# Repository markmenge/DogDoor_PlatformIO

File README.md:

This is an AI experiment. It is a work-in-progress. Check back later for when things start working.

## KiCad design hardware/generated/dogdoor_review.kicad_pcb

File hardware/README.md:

# DogDoor carrier PCB: engineering review draft

**Do not order this revision.** This is a reproducible design/routing exercise,
not a fabrication-approved or safety-certified door controller. No order is
placed, and no production Gerber ZIP is supplied until the checks below pass.
The existing firmware is unchanged.

## Open the project

Open `generated/dogdoor_review.kicad_pro` in KiCad 7. The project includes an
editable schematic, a placed board, a circuit manifest, and review BOM/placement
CSVs. The schematic uses embedded pin-by-pin review symbols, so it does not
need a downloaded symbol library. Footprints use your installed KiCad libraries.
The board is intentionally roomy: 140 x 100 mm, two copper layers.

J3 uses the bundled `BarrelJack_Horizontal.step` visual model in KiCad's 3D
viewer, rotated 90 degrees to match the existing PJ-102AH footprint. Both the
placed and routed boards reference it relative to the project directory; no
installed 3D library is needed for J3. This is a generic horizontal barrel-jack
visual approximation, not a manufacturer-certified PJ-102AH mechanical model.
The pads, wiring, and part selection are unchanged.
Model source: [KiCad packages3D, release 10.0.0](https://gitlab.com/kicad/libraries/kicad-packages3D/-/blob/10.0.0/Connector_BarrelJack.3dshapes/BarrelJack_Horizontal.step).
License: [CC BY-SA 4.0 with KiCad library exception](https://www.kicad.org/libraries/license/).

The bundled `Heltec_WiFi_Kit_32_V2.wrl` shows a visual-only module assembly
across J1/J2, including both socket rows, white PCB, OLED with cyan HELTEC text,
USB connector, and buttons. It is attached once to J1; J2's standalone socket
model is omitted because the assembly includes it. The header spacing is
22.86 mm with 18 pins per row at 2.54 mm pitch, USB toward pin 1 / board top.
Socket height is assumed to be 8.5 mm; module body is approximated as
26.06 x 50 x 1.6 mm. This is not a certified clearance or enclosure model.
No electrical features are changed. Run `hardware/heltec_model.py` to rebuild
the model alone; board generation rebuilds it with the selected row spacing.

## Confirmed requirements and assumptions

- Heltec WiFi Kit 32 V2, two 18-pin rows, USB end toward the top of the PCB.
- Along-row pitch is 2.54 mm (0.1 inch).
- Row separation is your confirmed **22.86 mm center-to-center (0.9 inch)**.
   Print `generated/socket_fit_check.pdf` at 100% and compare the real module
   as a final check before ordering; header sockets still need adequate height.
- Regulated 5 V, 3 A adapter, 2.1 mm center-positive plug.
- Two yellow TT motors, separate electrical outputs, same direction commands.
  They are NOT connected electrically in parallel on this PCB.
- HC-SR501 PIR outputs are assumed to be 3.3 V, not 5 V. Measure them first.
- Factory assembles fitted SMD parts; you solder sockets, connectors, and bulk
  capacitors. Sensor headers can be omitted and wires soldered into their holes.

## Circuit choices

U1/U2 are TI **DRV8876PWPR** HTSSOP MOSFET bridges. PMODE is HIGH for two-input
PWM control, compatible with the existing GPIO25/GPIO26 direction interface.
Both LOW means **coast**, not braking. Never assume the winch holds the door
when power is off: provide mechanical retention and independent obstruction
protection. Driver outputs must never be connected together.

Each bridge has a nominal **1.0 A current limit**, not a 2 A setting. VREF is
nominally 1.65 V from a 10k/10k divider on the Heltec 3.3 V output. A 1.50k
IPROPI resistor and the datasheet's 1100 uA/A current mirror give:

`Itrip = 1.65 / (1500 * 0.0011) = 1.0 A`

This is winding current regulation, not a precise total adapter-current limit.
Sense tolerance, startup overshoot, capacitor inrush, motor loading, and ESP32
Wi-Fi consumption still require bench measurement. Two TT motors can exceed
the 3 A supply at stall without limiting. The limited motors may not lift the
door. Do not raise the limit blindly; measure load and reassess supply/thermal
requirements. The driver's 3.5 A specification is a peak rating, not permission
to run that current continuously on this layout.

IMODE floats intentionally: fixed-off-time chopping with latched-off overcurrent
protection. Do not add a pull-down there. Removing/reclosing the stop loop resets
sleep and can re-enable the outputs if the firmware still commands movement.

J5 is a normally-closed stop-loop connection to nSLEEP. With it open, both
drivers are disabled. This is a bench inhibit, not a certified emergency stop;
it causes coasting and does not cut power. Use a proper motor-power disconnect
and mechanical safety measures for the installed door.

VM is fed through a 3 A fuse. The driver requires **at least 4.5 V at its VM pin**:
your nominal 5 V leaves only 0.5 V for adapter sag, cable, jack, fuse, and traces.
Measure under simultaneous starting and worst permitted load. F1 requires an
inrush/time-current review; it does not regulate current or protect an animal.
There is **no reverse-polarity or wrong-voltage protection** in this draft.
Do not plug an Arduino 9 V/12 V adapter into the same-looking socket.

The controller branch uses SS34 isolation, a low-DCR ferrite, 470 uF, and ceramic
decoupling. It shares the adapter with VM: filtering does not fix sustained supply
sag. JP1 disconnects the Heltec 5 V feed. Remove JP1 before powering by USB;
do not rely on the carrier diode to resolve the Heltec's internal power paths.
Confirm the revision-specific Heltec schematic before simultaneous power sources.

The bridges have 22 nF charge-pump flying capacitors, 100 nF VCP-to-VM capacitors,
100 nF VM bypasses, and 10 uF local ceramics. Add 100 nF suppression capacitors
directly at each motor, with short leads and twisted motor wires. The bulk
capacitors do not substitute for short, low-resistance motor power wiring.

GPIO35 receives the combined open-drain fault outputs. GPIO34 and GPIO36 receive
the two current-sense signals. Existing firmware does not read these signals:
do not assume an automatic stop on driver fault or excessive load is implemented.

## Connection table

| Reference | Connection |
| --- | --- |
| J1/J2 | Female Heltec sockets; pin 1 at USB end on each row |
| J3 | CUI PJ-102AH, center-positive 5 V only, 2.1 mm |
| J4 | Alternate power screw terminal: pin 1 +5 V, pin 2 GND; use ONE input |
| J6 | Motor A: pins 1/2 motor leads |
| J7 | Motor B: pins 1/2 motor leads; swap one motor's leads if mechanically opposed |
| J8/J9 | PIR inside/outside: pin 1 +5 V, pin 2 OUT (3.3 V only), pin 3 GND |
| J10/J11 | Open/closed reed: pin 1 switch signal, pin 2 GND; passive contacts only |
| J5 | Normally-closed bench inhibit loop; open = both bridges disabled |
| JP1 | Shunt for carrier-powered Heltec; REMOVE before USB power |

Socket row labels and numbers come from the local V2 pinout PDF, not from a
generic ESP32 DevKit footprint. Vext, OLED pins, and unused module pins are left
unconnected. Only one module 3.3 V header pin feeds the reference/control circuit.

GPIO2 and GPIO12 are boot straps. The fitted R40/R42 zero-ohm links preserve the
current firmware, but cold boots must be tested with PIR HIGH/LOW and reed open/
closed. No external pull-up is added to GPIO12. Before production, prefer moving
PIR_OUT to GPIO22 and LIMIT_CLOSE to GPIO27: remove R40/R42, fit R41/R43, and
change the corresponding firmware constants. Never fit both options at once.

## Generate again

From the workspace root in PowerShell:

```powershell
& 'C:/Program Files/Python311/python.exe' hardware/generate.py --self-test
& 'D:/Program Files/KiCad/7.0/bin/python.exe' hardware/generate.py
& 'D:/Program Files/KiCad/7.0/bin/python.exe' hardware/generate.py --row-spacing 22.86
& 'D:/Program Files/KiCad/7.0/bin/python.exe' hardware/generate.py --route "$env:LOCALAPPDATA/DogDoorPCB/freerouting-2.5.0/freerouting-2.5.0.jar"
& 'C:/Program Files/Python311/python.exe' hardware/review.py
& 'C:/Program Files/Python311/python.exe' hardware/review.py --session hardware/generated/dogdoor_review.ses
& 'D:/Program Files/KiCad/7.0/bin/python.exe' hardware/generate.py --import-routing hardware/generated/dogdoor_review.routing.json
```

**Generation overwrites generated files, including manual PCB edits.** Make a
separate working copy of the project before editing. The generator checks circuit
assignments, KiCad-parsed schematic connectivity, and all assigned PCB pads.
It does not certify analog behavior, footprint fit, component sourcing, or safety.

FreeRouting 2.5.0 was downloaded from the official GitHub release and checked
against its published SHA-256. Its native Windows build crashed on board snapshot
serialization, so use the JAR with a portable Java 25 runtime under local app-data.
The generator discovers that runtime automatically; `--java` can override it.
Your existing system Java installation is unchanged.

## Routing and remaining PCB work

The generator exports DSN and FreeRouting produces SES. In PCB Editor, use
**File > Import > Specctra Session** to import `dogdoor_review.ses`, then save.
The autorouter is a layout assistant, not electrical sign-off.

1. **Fit first.** Print a 1:1 board drawing with scaling disabled; verify the
   printed 2.54 mm pitch and row spacing with a ruler, then compare your module.
   Measure pin centers, not outside edges. Both rows must enter female sockets
   without bending pins. Verify USB overhang/access and antenna position.
2. **Power paths.** Highlight INPUT_5V, VM, MOTOR_A1/A2, and MOTOR_B1/B2. Their
   draft net class requests 1.2 mm tracks and larger vias; the tiny HTSSOP pads
   need short 0.3 mm escape sections. Review actual copper width, neck-down
   length, via ampacity, voltage drop, and temperature, not only net-class names.
   Use wider copper pours for the 3 A feeder where practical. Route each motor's
   return through the driver/ground plane, not through the module/sensor area.
3. **Ground and heat.** Add continuous GND pours on both layers and refill with
   B. Connect U1/U2 exposed pads and nearby ground pins to substantial copper,
   with thermal vias and stitching. Do not make the ESP32 ground path the sole
   motor return. Confirm copper area against TI's layout/thermal guidance. The
   standard footprint includes 0.2 mm thermal drills: confirm fabricator support
   and solder-wicking/paste requirements with the assembly house.
4. **Critical capacitors.** Inspect C10/C20 (CPH-CPL), C11/C21 (VCP-VM), and
   C12/C22 (VM-GND). Short direct loops matter; fix router detours around these
   pins. R10/R20 should connect directly to IPROPI and local quiet ground. Keep
   VREF/current-sense signals away from motor switching paths.
5. **Antenna.** Confirm the actual antenna outline. The draft bottom-of-module
   keep-out excludes copper/tracks/vias on both layers. Expand or move it to the
   module maker's required region; avoid nearby metal, motors, and enclosure walls.
6. **Rules and labels.** Run Inspect > Design Rules Checker. Fix every clearance,
   short, unrouted connection, courtyard conflict, and edge violation; review
   warnings individually. Do not blindly exclude errors. Move silk away from pads,
   enlarge illegible labels, and mark polarity/pin 1 clearly. Check the socket's
   female numbering versus the view in the PDF, not only 3D appearance.
7. **Schematic checks.** Run schematic ERC manually (KiCad 7 has no CLI ERC here).
   The embedded review symbols use passive pins and therefore do not catch all
   electrical-type mistakes; independently review the TI PWP pinout and every
   power/control connection. Do not update the PCB from a generic replacement
   symbol without checking pin mapping and footprint association.

## Actual routing result and repairs

**Latest manually repaired board:** `generated/dogdoor_review_routed.kicad_pcb`.
The saved `generated/DRC.rpt` dated 2026-10-12 reports zero DRC violations,
zero unconnected pads, and zero footprint errors. The following routing counts
describe the initial autorouter output, before those manual repairs. Clean DRC
does not approve motor-current capacity, thermal layout, sourcing, or safety.
Do not regenerate or reimport the old routing session over the repaired board.

Open `generated/dogdoor_review_routed.kicad_pro` for the routed draft. The placed
project is separate. Regeneration overwrites both, so make a copy before manual
layout work. `review.py` requires PyMuPDF and sexpdata in system Python, while
`generate.py` uses KiCad's bundled Python.

The Java FreeRouting run completed three passes and reported 12 unrouted items
with no router-rule violations. The imported KiCad board contains 43 vias.
KiCad's independent `generated/routed_drc.txt` identifies **8 missing connections,
50 minimum-track-width errors, and 12 dangling-track/via warnings**. No clearance,
short-circuit, or footprint errors were reported. This is not a clean DRC result.

In PCB Editor, run Inspect > Design Rules Checker, click each item to locate it,
and use Highlight Net to follow the intended connection. Route with X from the
existing pad/track endpoint, not from an approximate point on the drawing.

| Unfinished net | Starting point / repair target |
| --- | --- |
| CLOSE | R5 pad 1 to the existing CLOSE route |
| FAULT | U2 pad 4 to the existing shared FAULT route |
| GND | Join the driver-area ground islands with properly reviewed ground copper |
| MOTOR_A2 | U1 OUT2/pad 10 escape to J6 pad 2 |
| MOTOR_B2 | U2 OUT2/pad 10 escape to J7 pad 2 |
| VM (three gaps) | Connect both VM/pad 11 escapes, local C11/C21 VM pads, and the shared motor supply |

FreeRouting necked down some routes to **0.15 mm**, narrower than the board's
**0.25 mm minimum**. Reroute/widen those sections; do not just lower the rule or
exclude the errors. Motor/power copper needs the wider 1.2 mm nominal route
outside short pad escapes, with further voltage-drop/thermal review as above.
Some preplaced escape stubs are locked: unlock only the affected track before
editing, preserving the IC pin-to-net connection. Remove genuinely unused stub
ends and one-layer-only vias after completing their nets, then rerun DRC.

## Factory assembly and ordering gate

The review BOM deliberately says REVIEW_REQUIRED for unselected supplier parts.
It is **not an upload-ready JLCPCB BOM**. Choose an assembly house, reserve actual
stock, and verify exact manufacturer part numbers, packages, voltage ratings,
capacitor DC-bias derating, ferrite DCR/current rating, jack current rating, and
connector hole sizes. Confirm DRV8876PWPR, not a different QFN package.

The placement CSV uses a bottom-left board origin with positive Y upward, top
side only. Factory rotation conventions vary: verify every pin-1/polarity preview,
especially the ICs and diode. Through-hole connectors and electrolytics are
marked HAND, and R41/R43 are DNP. Match the approved board version to BOM/CPL.

Only after independent electrical/layout review, fit checks, BOM review, and
zero unresolved manufacturing DRC errors should you plot Gerbers and Excellon
drills from the approved board. Inspect them in GerbView and the manufacturer's
preview. Request a small prototype batch, not a production run. This exercise
does not include paying for or submitting an order.

## First prototype bring-up

1. Keep the door mechanism disconnected. Remove the module, both motors, JP1,
   and the J5 inhibit loop. Inspect solder/polarity and check for power shorts.
2. Use a current-limited bench supply for first power-on; verify VM and filtered
   5 V before inserting the module. The ordinary 3 A adapter is not a substitute
   for a bench current limit during initial fault finding.
3. Power off, insert the module in the confirmed orientation, and enable its
   selected power path. Check 3.3 V, VREF (~1.65 V), nSLEEP LOW with J5 open,
   and output coasting. Leave the motor terminals unconnected for logic testing.
4. Connect one unloaded motor, enable J5, and pulse a direction briefly. Verify
   polarity, stop-loop behavior, sense current, and supply minimum voltage.
   Repeat for the other motor before running both. Do not deliberately hold a
   motor stalled to test the limit; use controlled load equipment.
5. Add suppression capacitors at the motors, verify both drive the drum in the
   same mechanical direction, then measure simultaneous-start and loaded current.
   Monitor IC/fuse/connector temperature and ESP32 reset behavior. Stop if the
   VM supply drops below specification or the assembly heats excessively.
6. Verify all cold-boot sensor states, both limits, wire-break cases, inhibit,
   OTA, Wi-Fi loss, and power-off behavior. Current firmware has no debug run
   timeout and ignores the new current/fault inputs; fix the safety behavior
   before connecting a working door. PIRs are not obstruction safety sensors.

## References

- Local `../WIFI_Kit_32_pinoutDiagram_V2.pdf` and V2 schematic.
- TI DRV8876 datasheet: https://www.ti.com/lit/ds/symlink/drv8876.pdf
- FreeRouting releases: https://github.com/freerouting/freerouting/releases

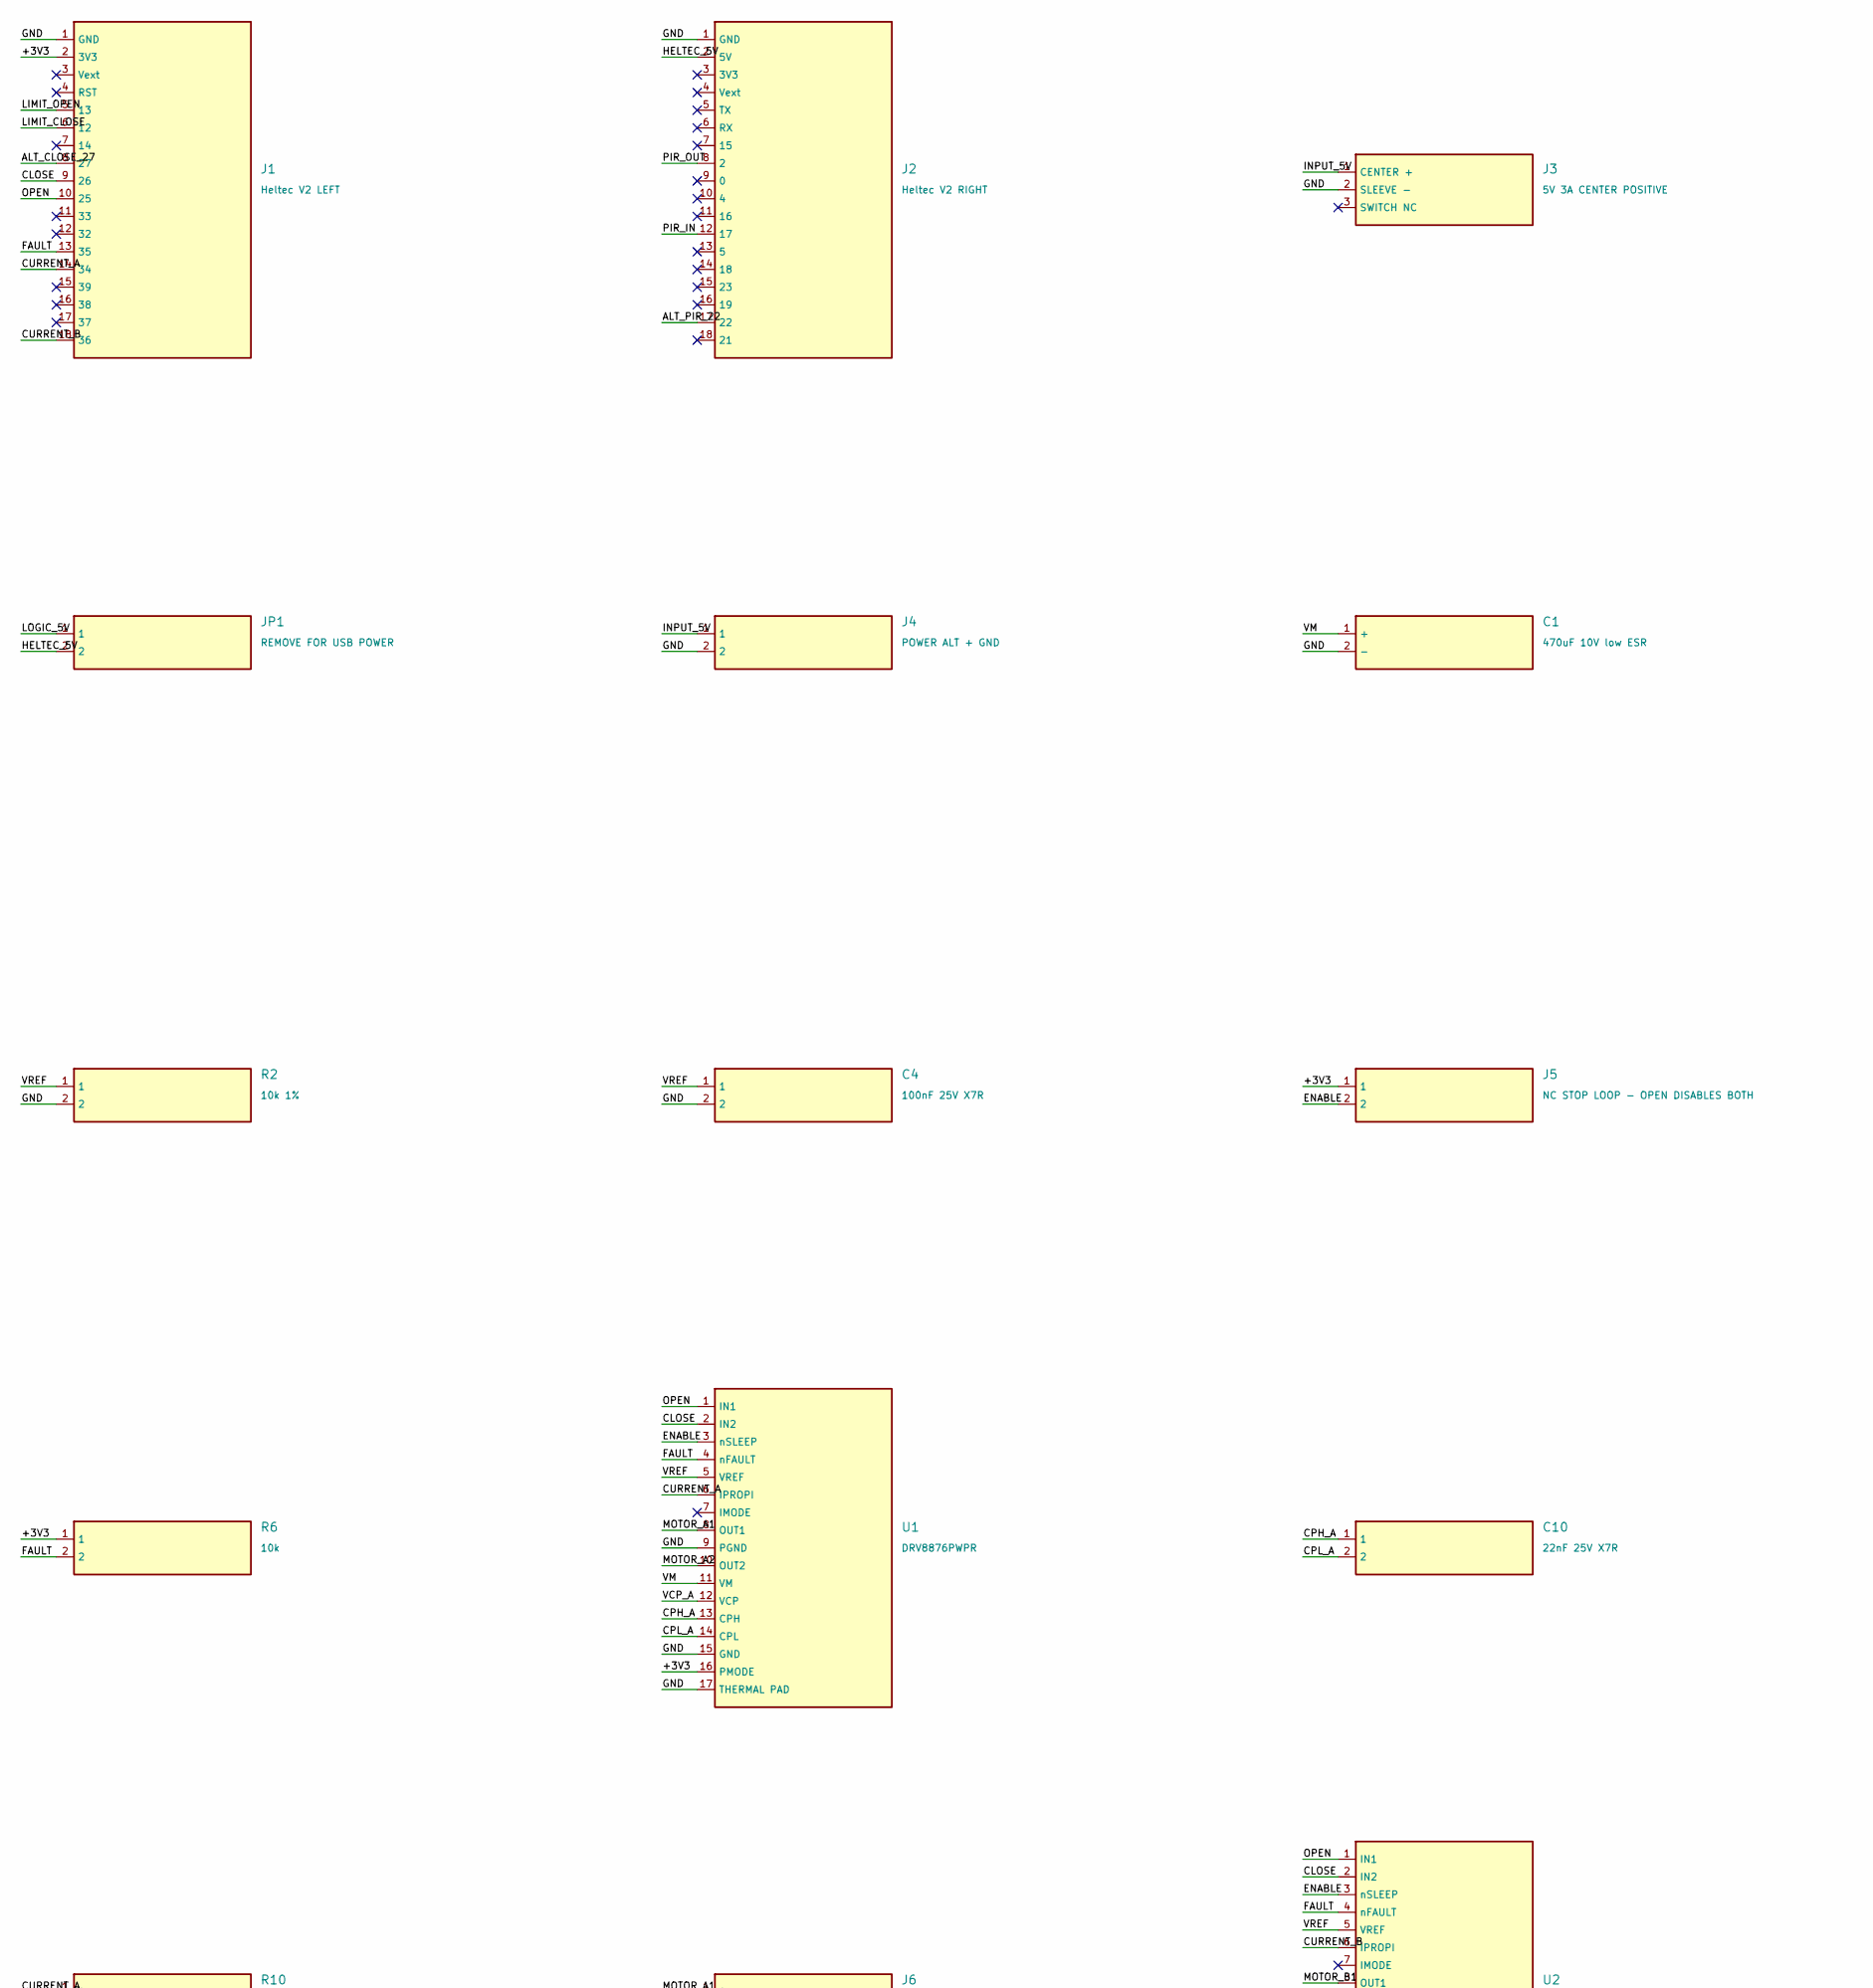
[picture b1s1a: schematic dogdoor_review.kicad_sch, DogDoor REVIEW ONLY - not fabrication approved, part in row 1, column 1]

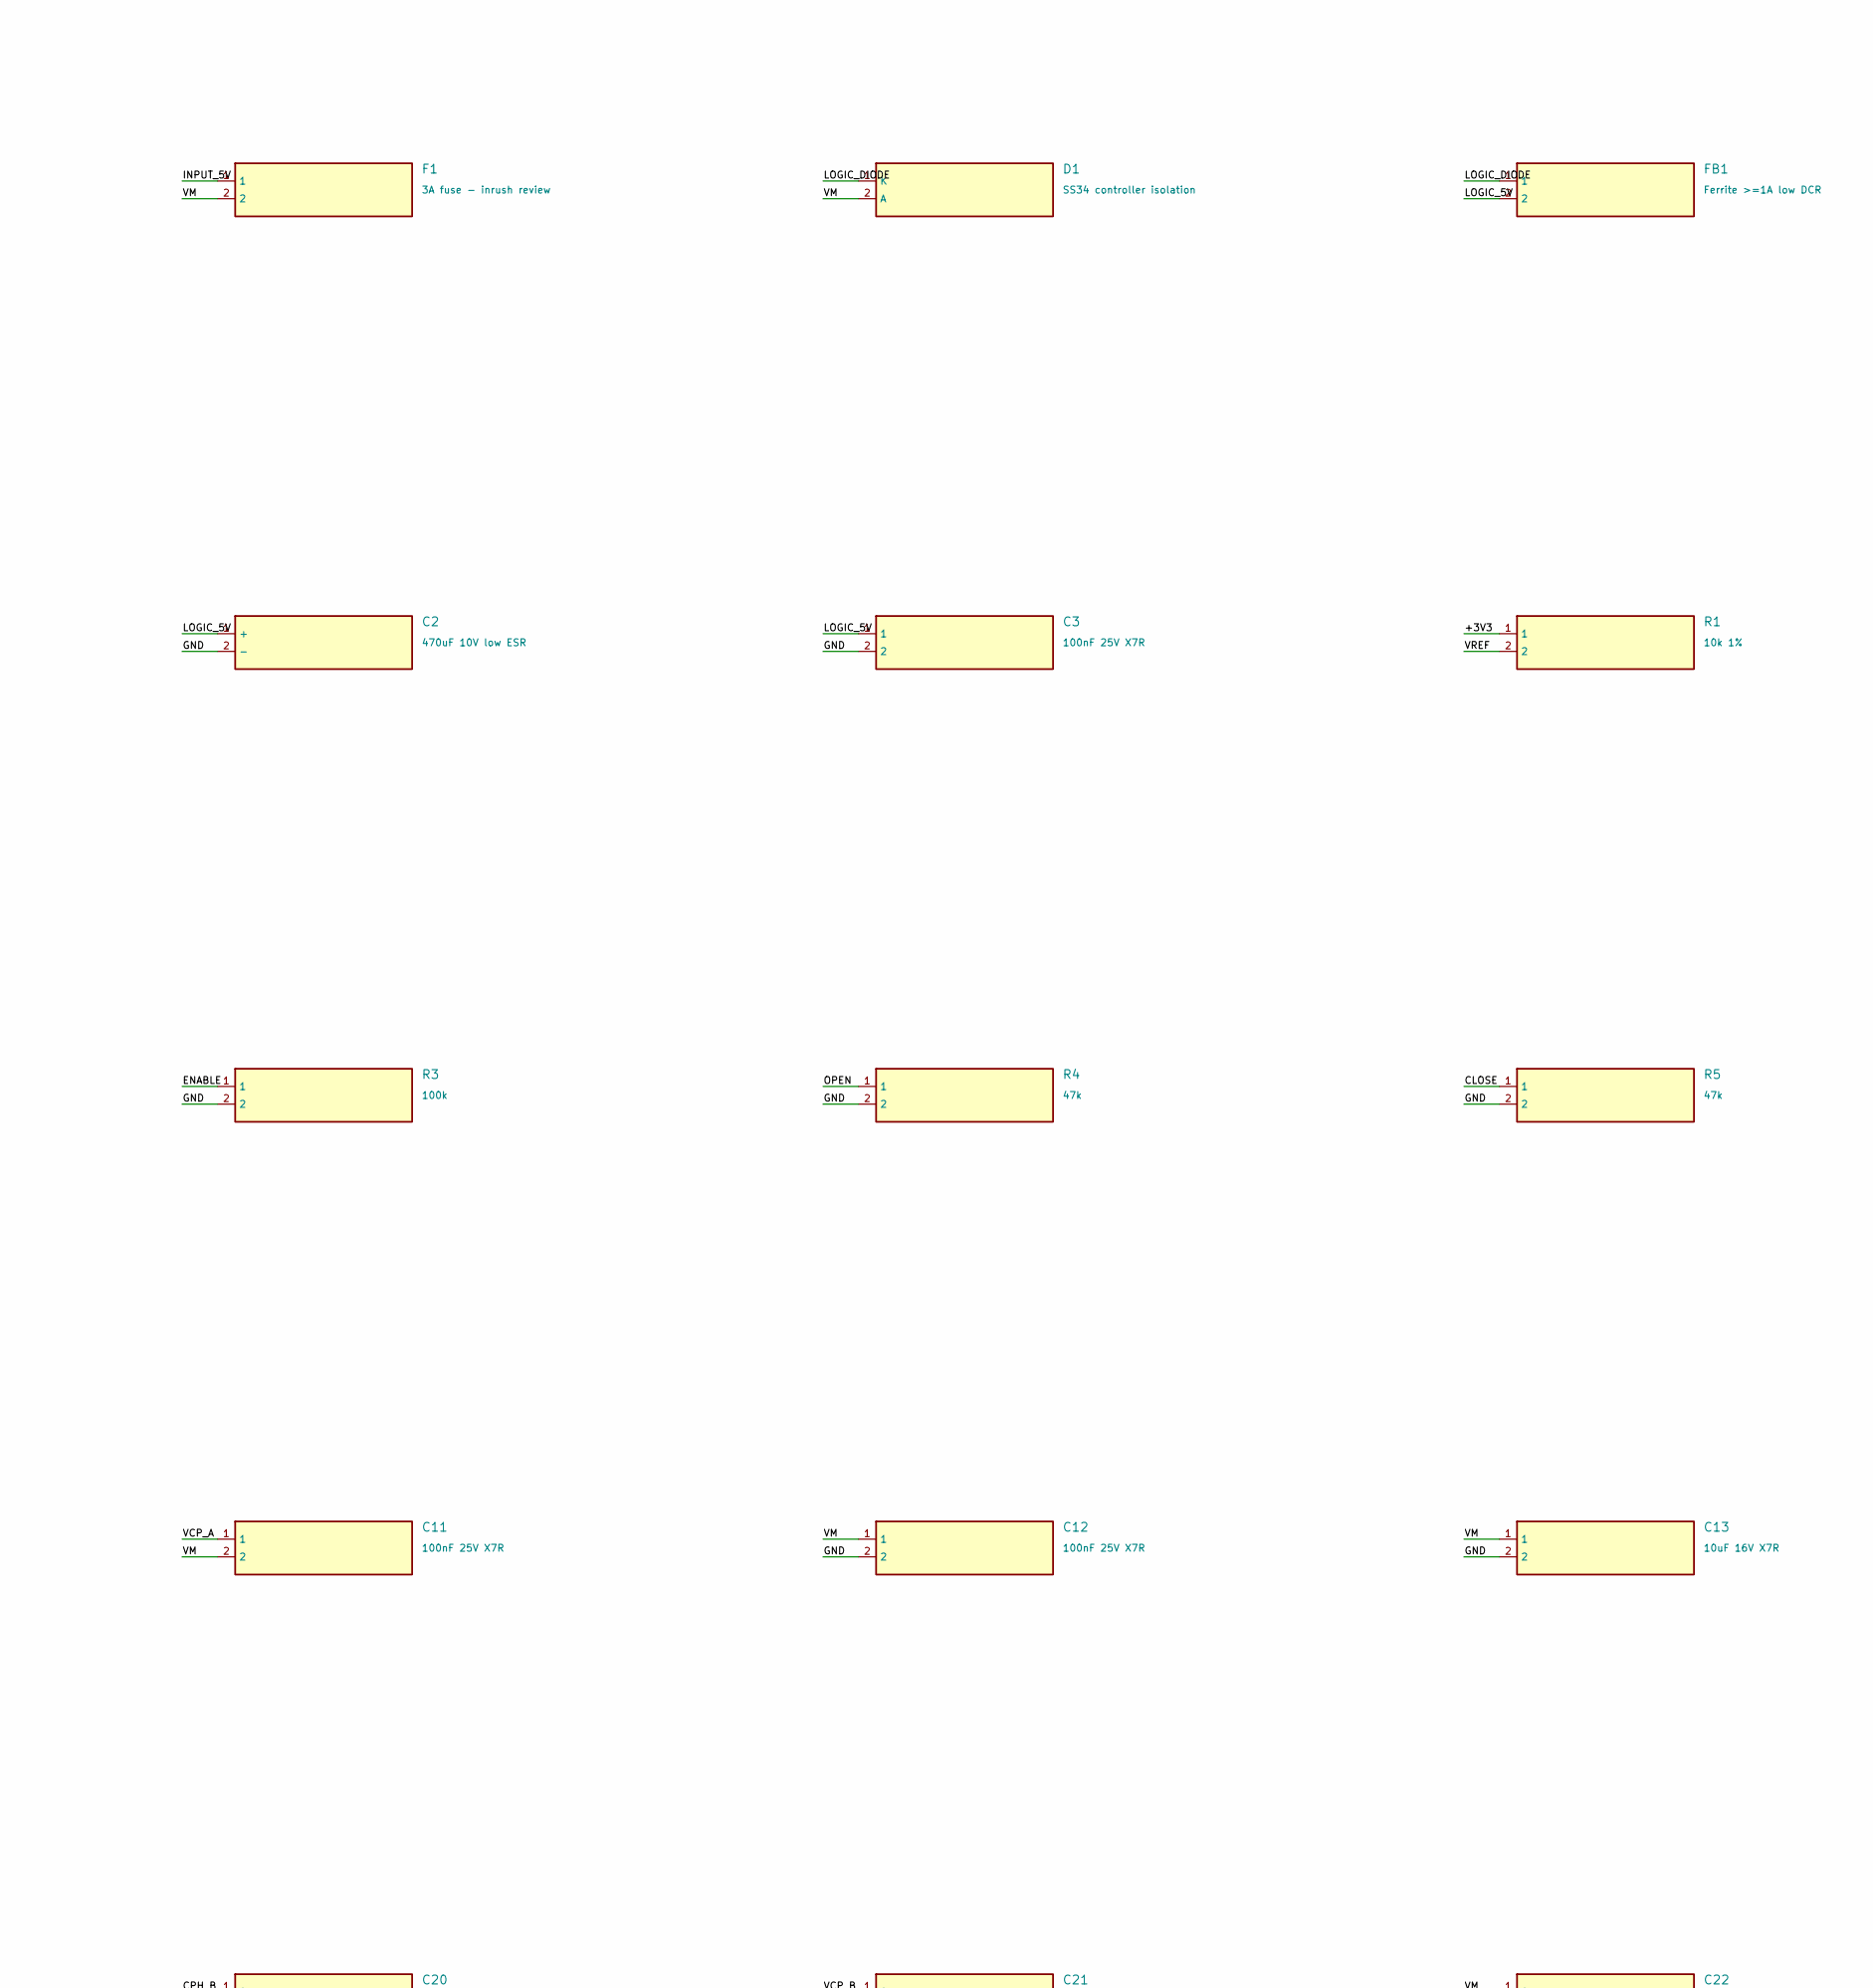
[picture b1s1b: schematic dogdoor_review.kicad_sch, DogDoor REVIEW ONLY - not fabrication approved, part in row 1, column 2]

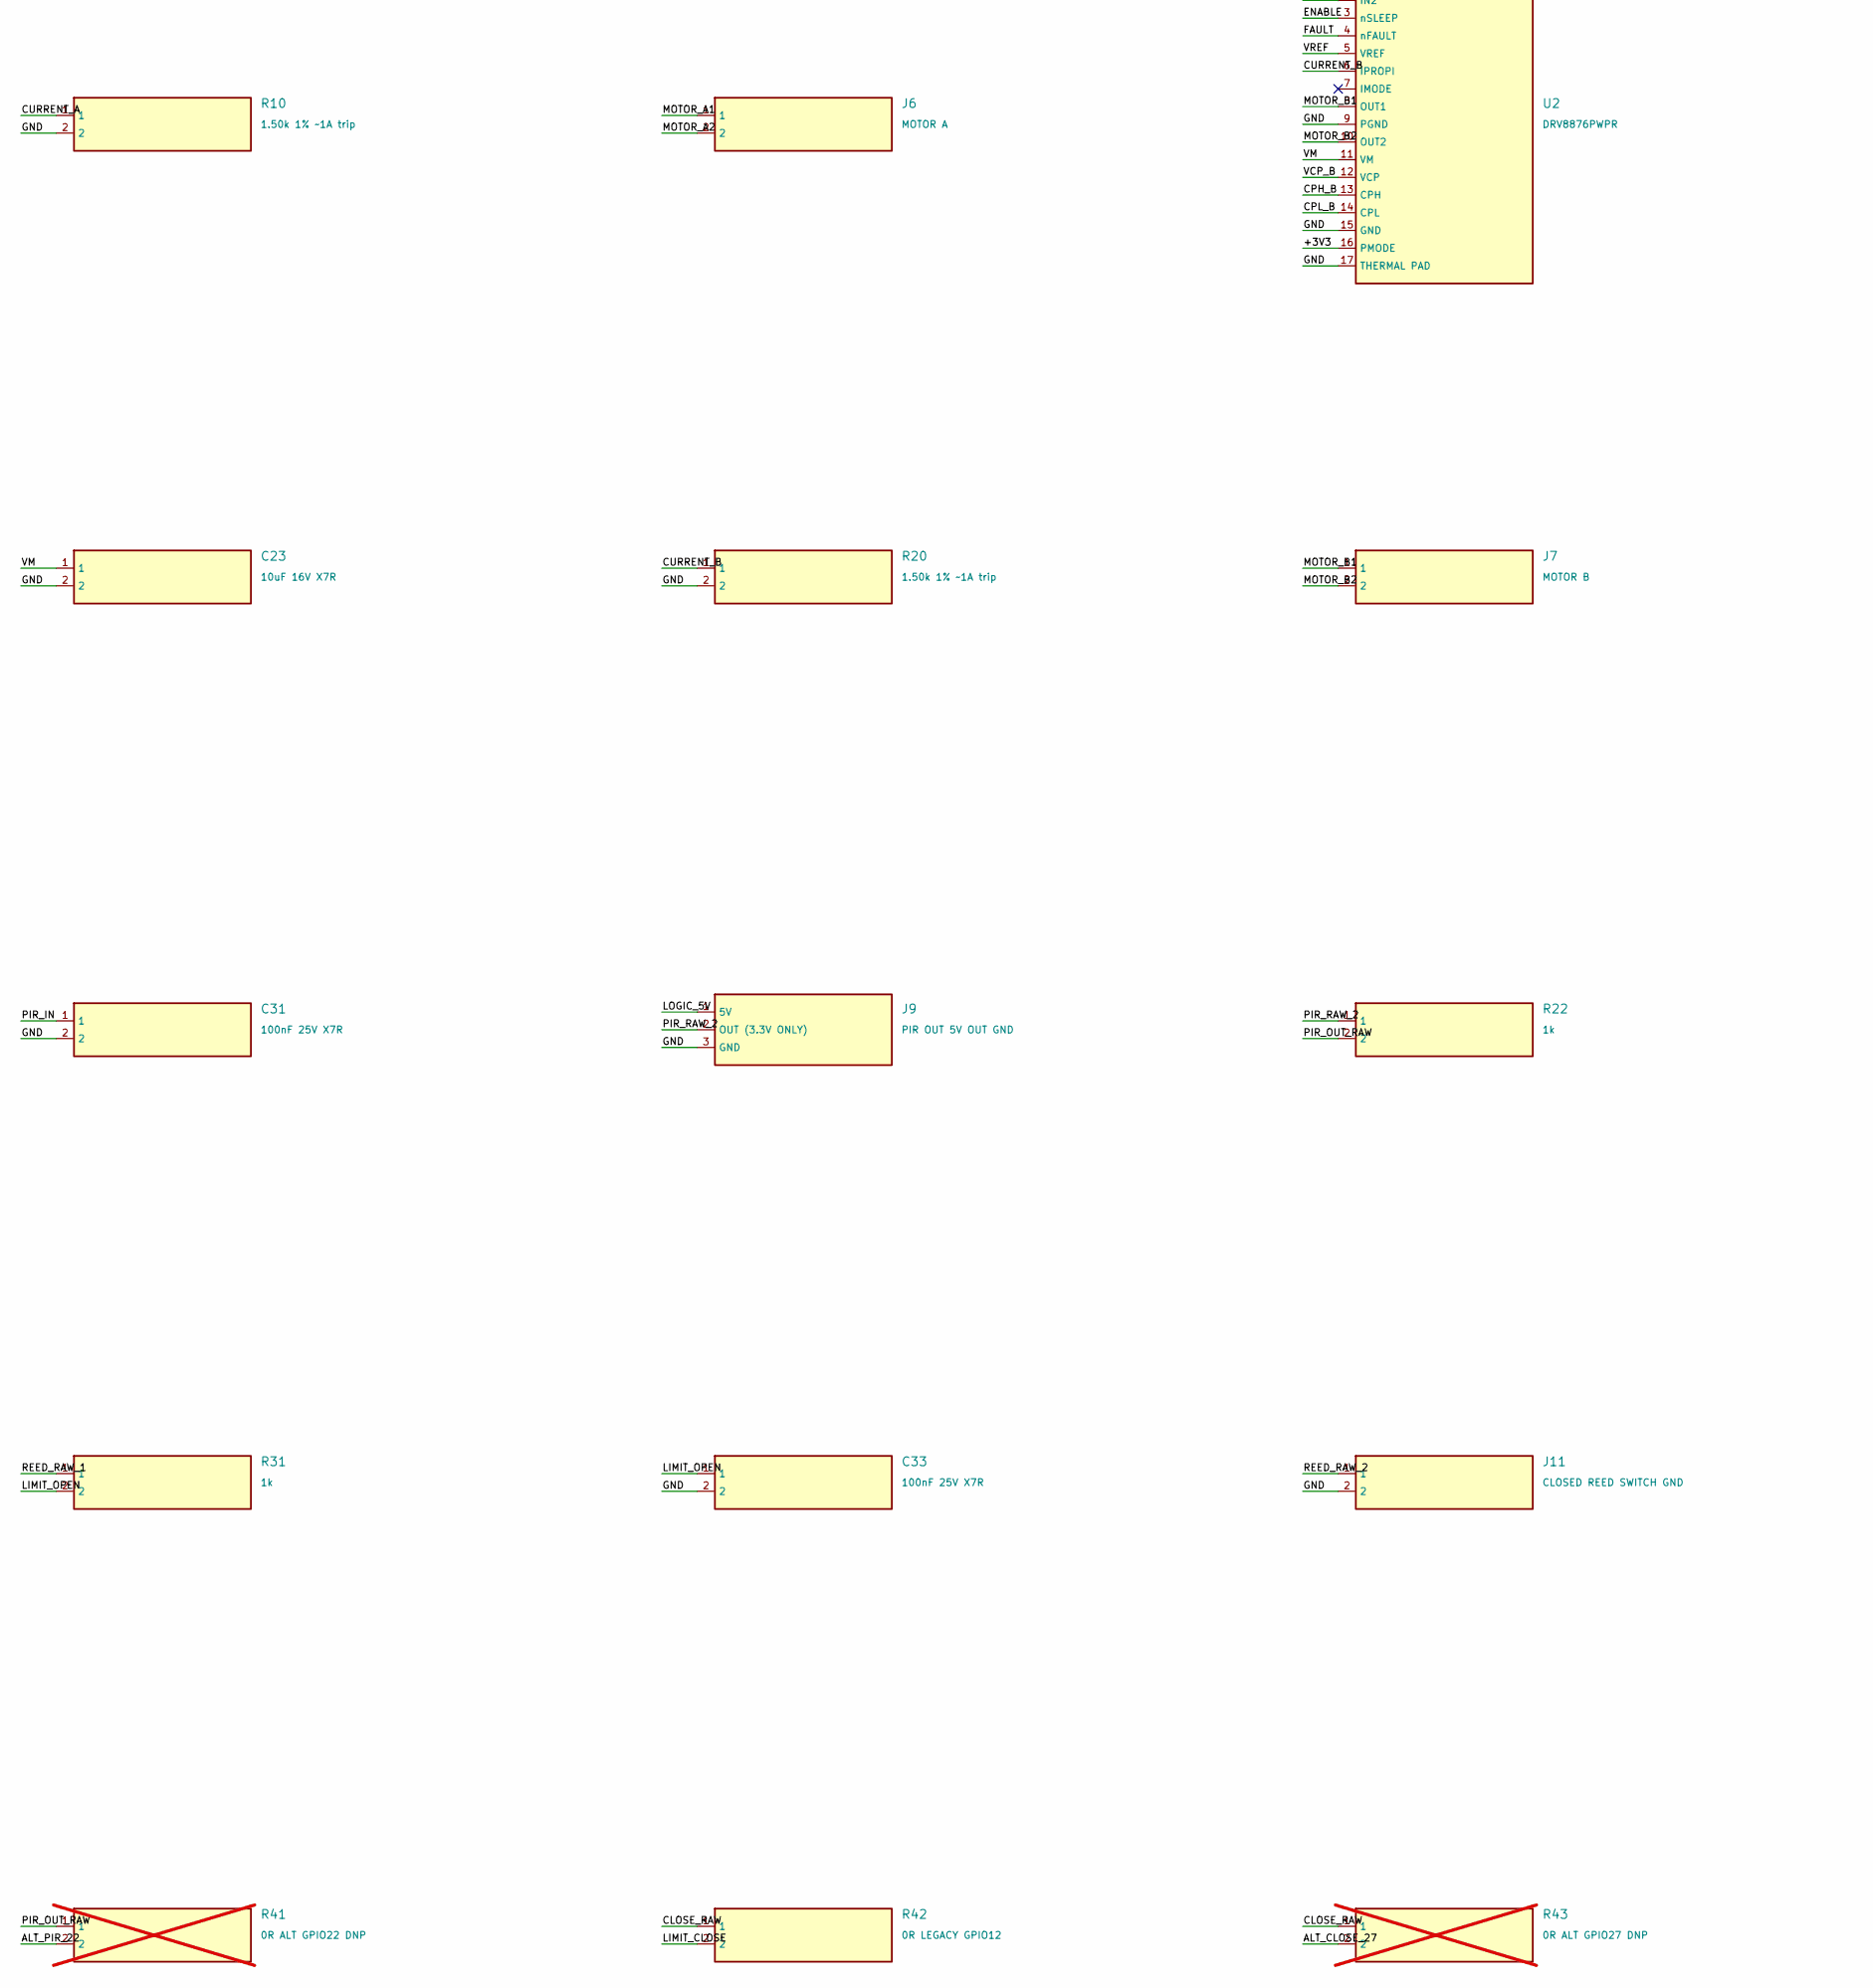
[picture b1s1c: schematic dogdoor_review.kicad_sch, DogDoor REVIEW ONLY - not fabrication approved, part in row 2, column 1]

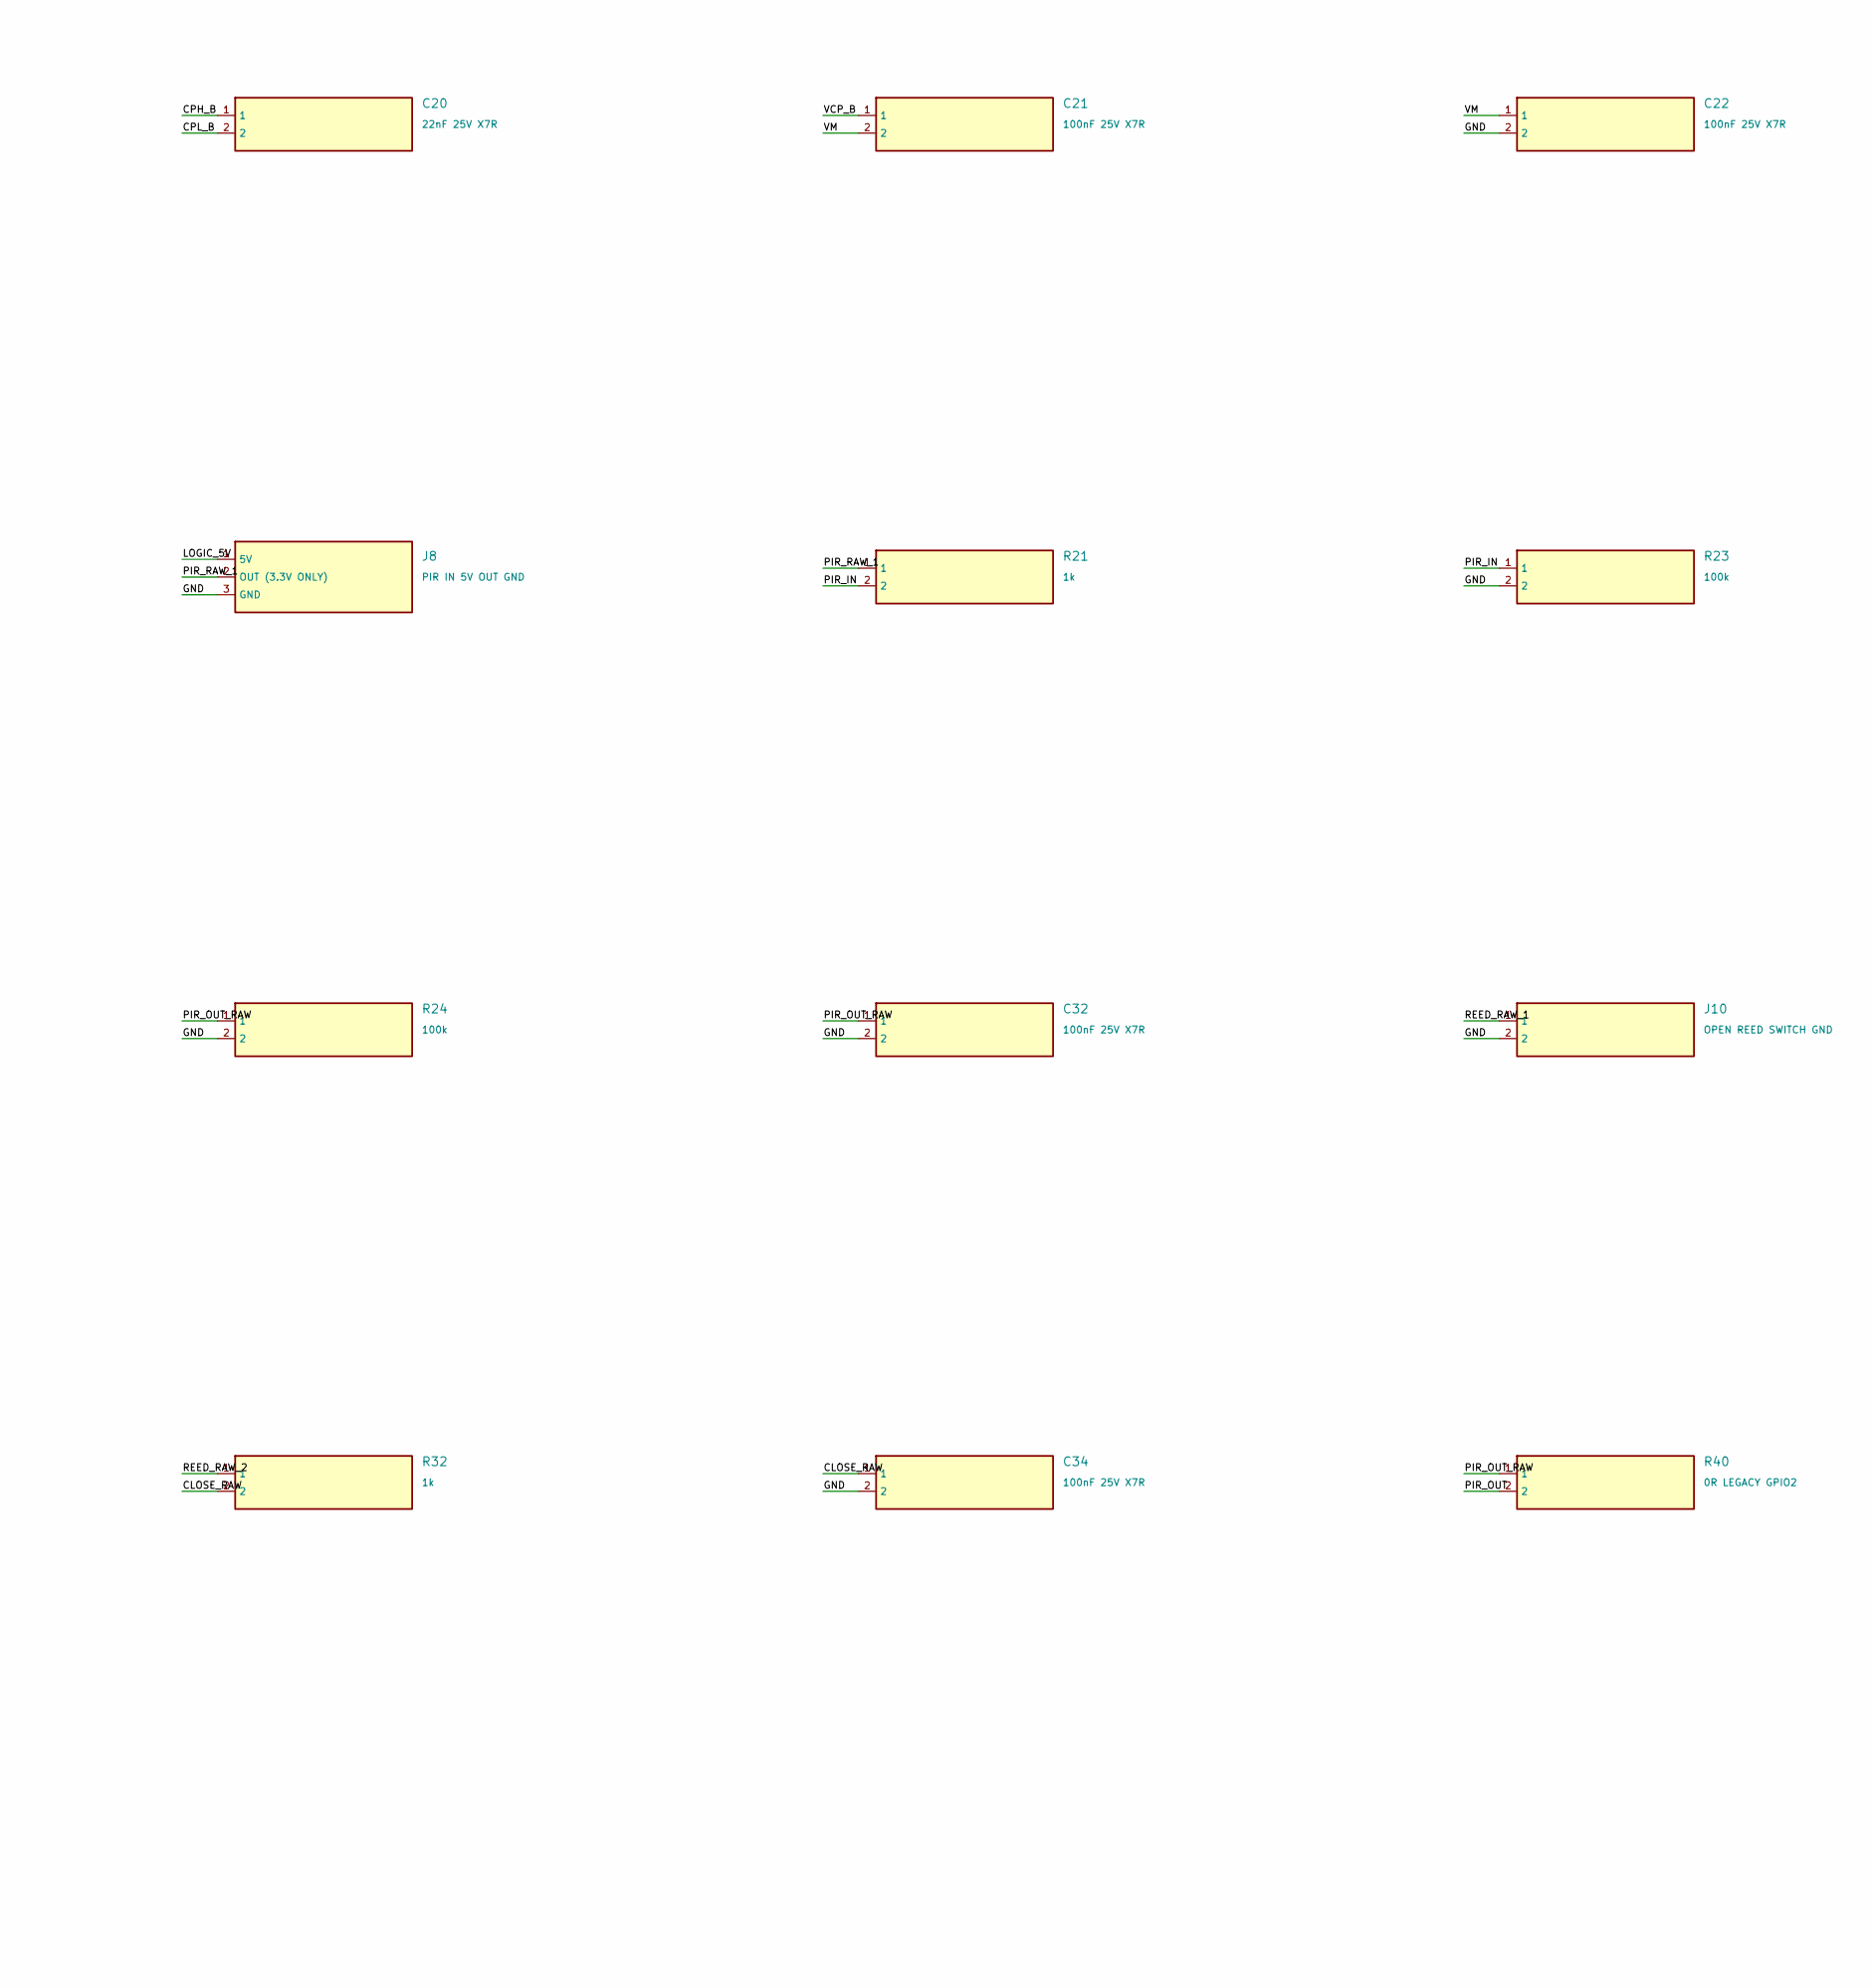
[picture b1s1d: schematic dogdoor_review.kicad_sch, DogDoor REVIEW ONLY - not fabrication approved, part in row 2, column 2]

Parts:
C1, C2: 470uF 10V low ESR; CP_Radial_D8.0mm_P3.50mm
C3, C4, C11, C12, C21, C22, C31, C32, C33, C34: 100nF 25V X7R; C_0805_2012Metric
C10, C20: 22nF 25V X7R; C_0805_2012Metric
C13, C23: 10uF 16V X7R; C_0805_2012Metric
D1: SS34 controller isolation; D_SMA
F1: 3A fuse - inrush review; Fuse_1206_3216Metric
FB1: Ferrite >=1A low DCR; L_1206_3216Metric
J1: Heltec V2 LEFT; PinSocket_1x18_P2.54mm_Vertical
J2: Heltec V2 RIGHT; PinSocket_1x18_P2.54mm_Vertical
J3: 5V 3A CENTER POSITIVE; BarrelJack_CUI_PJ-102AH_Horizontal
J4: POWER ALT + GND; TerminalBlock_Phoenix_MKDS-1,5-2-5.08_1x02_P5.08mm_Horizont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
J5: NC STOP LOOP - OPEN DISABLES BOTH; PinHeader_1x02_P2.54mm_Vertical
J6: MOTOR A; TerminalBlock_Phoenix_MKDS-1,5-2-5.08_1x02_P5.08mm_Horizont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
J7: MOTOR B; TerminalBlock_Phoenix_MKDS-1,5-2-5.08_1x02_P5.08mm_Horizont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
J8: PIR IN 5V OUT GND; PinHeader_1x03_P2.54mm_Vertical
J9: PIR OUT 5V OUT GND; PinHeader_1x03_P2.54mm_Vertical
J10: OPEN REED SWITCH GND; PinHeader_1x02_P2.54mm_Vertical
J11: CLOSED REED SWITCH GND; PinHeader_1x02_P2.54mm_Vertical
JP1: REMOVE FOR USB POWER; PinHeader_1x02_P2.54mm_Vertical
R1, R2: 10k 1%; R_0805_2012Metric
R3, R23, R24: 100k; R_0805_2012Metric
R4, R5: 47k; R_0805_2012Metric
R6: 10k; R_0805_2012Metric
R10, R20: 1.50k 1% ~1A trip; R_0805_2012Metric
R21, R22, R31, R32: 1k; R_0805_2012Metric
R40: 0R LEGACY GPIO2; R_0805_2012Metric
R41: 0R ALT GPIO22 DNP; R_0805_2012Metric; not fitted
R42: 0R LEGACY GPIO12; R_0805_2012Metric
R43: 0R ALT GPIO27 DNP; R_0805_2012Metric; not fitted
U1, U2: DRV8876PWPR; HTSSOP-16-1EP_4.4x5mm_P0.65mm_EP3.4x5mm_Mask2.46x2.31mm_The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

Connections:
+3V3: J1.2 (3V3), J5.1, R1.1, R6.1, U1.16 (PMODE), U2.16 (PMODE)
ALT_CLOSE_27: J1.8 (27), R43.2
ALT_PIR_22: J2.17 (22), R41.2
CLOSE: J1.9 (26), R5.1, U1.2 (IN2), U2.2 (IN2)
CLOSE_RAW: C34.1, R32.2, R42.1, R43.1
CPH_A: C10.1, U1.13 (CPH)
CPH_B: C20.1, U2.13 (CPH)
CPL_A: C10.2, U1.14 (CPL)
CPL_B: C20.2, U2.14 (CPL)
CURRENT_A: J1.14 (34), R10.1, U1.6 (IPROPI)
CURRENT_B: J1.18 (36), R20.1, U2.6 (IPROPI)
ENABLE: J5.2, R3.1, U1.3 (nSLEEP), U2.3 (nSLEEP)
FAULT: J1.13 (35), R6.2, U1.4 (nFAULT), U2.4 (nFAULT)
GND: C1.2 (-), C2.2 (-), C3.2, C4.2, C12.2, C13.2, C22.2, C23.2, C31.2, C32.2, C33.2, C34.2, J1.1 (GND), J2.1 (GND), J3.2 (SLEEVE -), J4.2, J8.3 (GND), J9.3 (GND), J10.2, J11.2, R2.2, R3.2, R4.2, R5.2, R10.2, R20.2, R23.2, R24.2, U1.9 (PGND), U1.15 (GND), U1.17 (THERMAL PAD), U2.9 (PGND), U2.15 (GND), U2.17 (THERMAL PAD)
HELTEC_5V: J2.2 (5V), JP1.2
INPUT_5V: F1.1, J3.1 (CENTER +), J4.1
LIMIT_CLOSE: J1.6 (12), R42.2
LIMIT_OPEN: C33.1, J1.5 (13), R31.2
LOGIC_5V: C2.1 (+), C3.1, FB1.2, J8.1 (5V), J9.1 (5V), JP1.1
LOGIC_DIODE: D1.1 (K), FB1.1
MOTOR_A1: J6.1, U1.8 (OUT1)
MOTOR_A2: J6.2, U1.10 (OUT2)
MOTOR_B1: J7.1, U2.8 (OUT1)
MOTOR_B2: J7.2, U2.10 (OUT2)
OPEN: J1.10 (25), R4.1, U1.1 (IN1), U2.1 (IN1)
PIR_IN: C31.1, J2.12 (17), R21.2, R23.1
PIR_OUT: J2.8 (2), R40.2
PIR_OUT_RAW: C32.1, R22.2, R24.1, R40.1, R41.1
PIR_RAW_1: J8.2 (OUT (3.3V ONLY)), R21.1
PIR_RAW_2: J9.2 (OUT (3.3V ONLY)), R22.1
REED_RAW_1: J10.1, R31.1
REED_RAW_2: J11.1, R32.1
VCP_A: C11.1, U1.12 (VCP)
VCP_B: C21.1, U2.12 (VCP)
VM: C1.1 (+), C11.2, C12.1, C13.1, C21.2, C22.1, C23.1, D1.2 (A), F1.2, U1.11 (VM), U2.11 (VM)
VREF: C4.1, R1.2, R2.1, U1.5 (VREF), U2.5 (VREF)
